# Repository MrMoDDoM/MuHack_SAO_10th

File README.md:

# MuHack_SAO_10th
Repo for the commemorative MuHack SAO fot the 10th anniversary

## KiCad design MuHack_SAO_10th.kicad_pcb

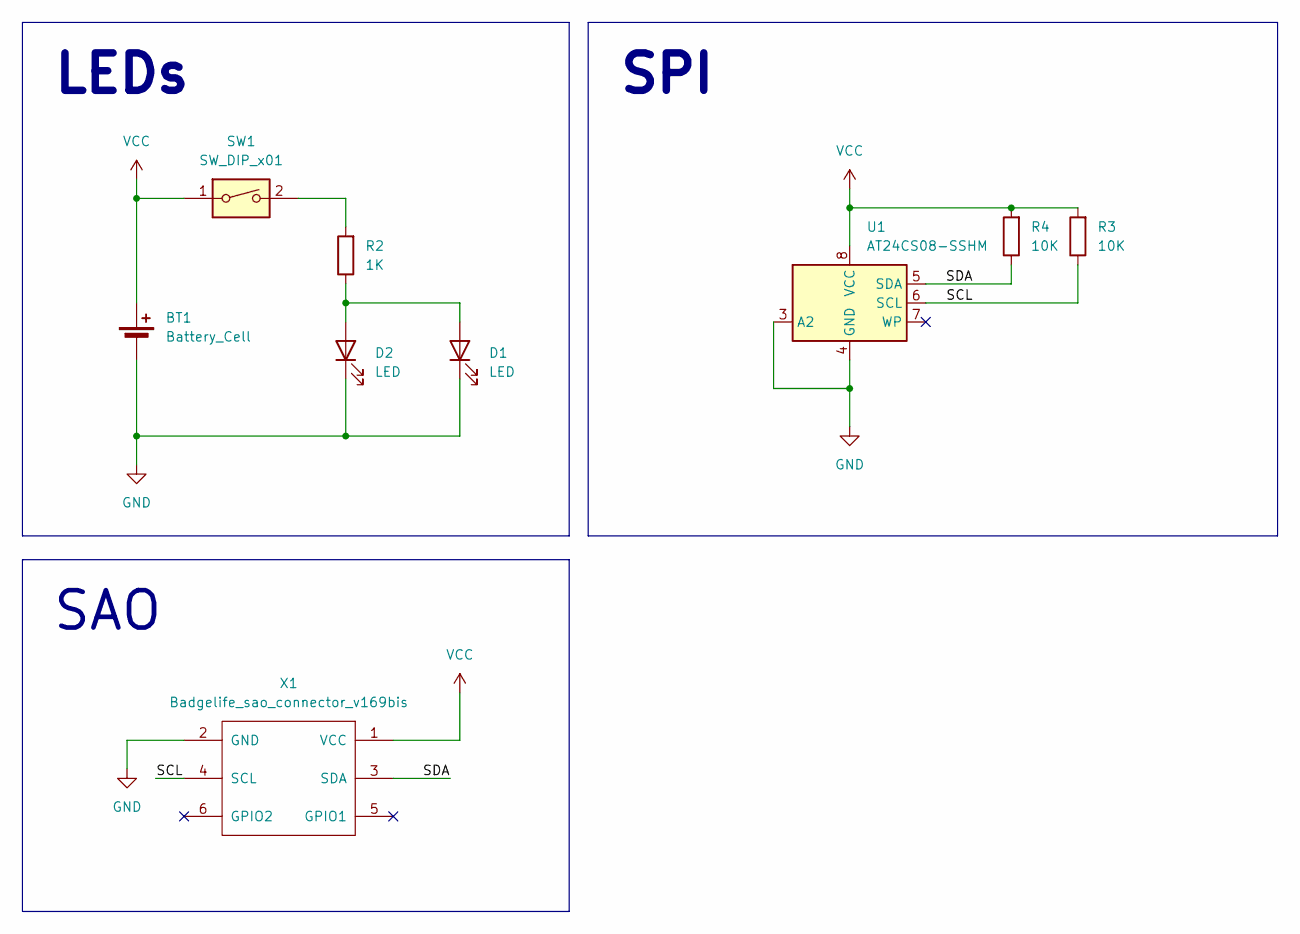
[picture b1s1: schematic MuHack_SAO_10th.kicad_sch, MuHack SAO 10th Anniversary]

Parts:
BT1: Battery_Cell; BatteryHolder_Keystone_3002_1x2032
D1, D2: LED; LED_0805_2012Metric_Pad1.15x1.40mm_HandSolder
R2: 1K; R_0805_2012Metric_Pad1.20x1.40mm_HandSolder
R3, R4: 10K; R_0805_2012Metric_Pad1.20x1.40mm_HandSolder
SW1: SW_DIP_x01; SW_SPDT_PCM12
U1: AT24CS08-SSHM; SOIC-8_3.9x4.9mm_P1.27mm
X1: Badgelife_sao_connector_v169bis; PinHeader_2x03_P2.54mm_Vertical_SMD

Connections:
/SCL: R3.1, U1.6 (SCL), X1.4 (SCL)
/SDA: R4.1, U1.5 (SDA), X1.3 (SDA)
GND: BT1.2 (-), D1.1 (K), D2.1 (K), U1.3 (A2), U1.4 (GND), X1.2 (GND)
unnamed: D1.2 (A), D2.2 (A), R2.1
unnamed: R2.2, SW1.2
VCC: BT1.1 (+), R3.2, R4.2, SW1.1, U1.8 (VCC), X1.1 (VCC)

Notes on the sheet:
LEDs
SAO
SPI

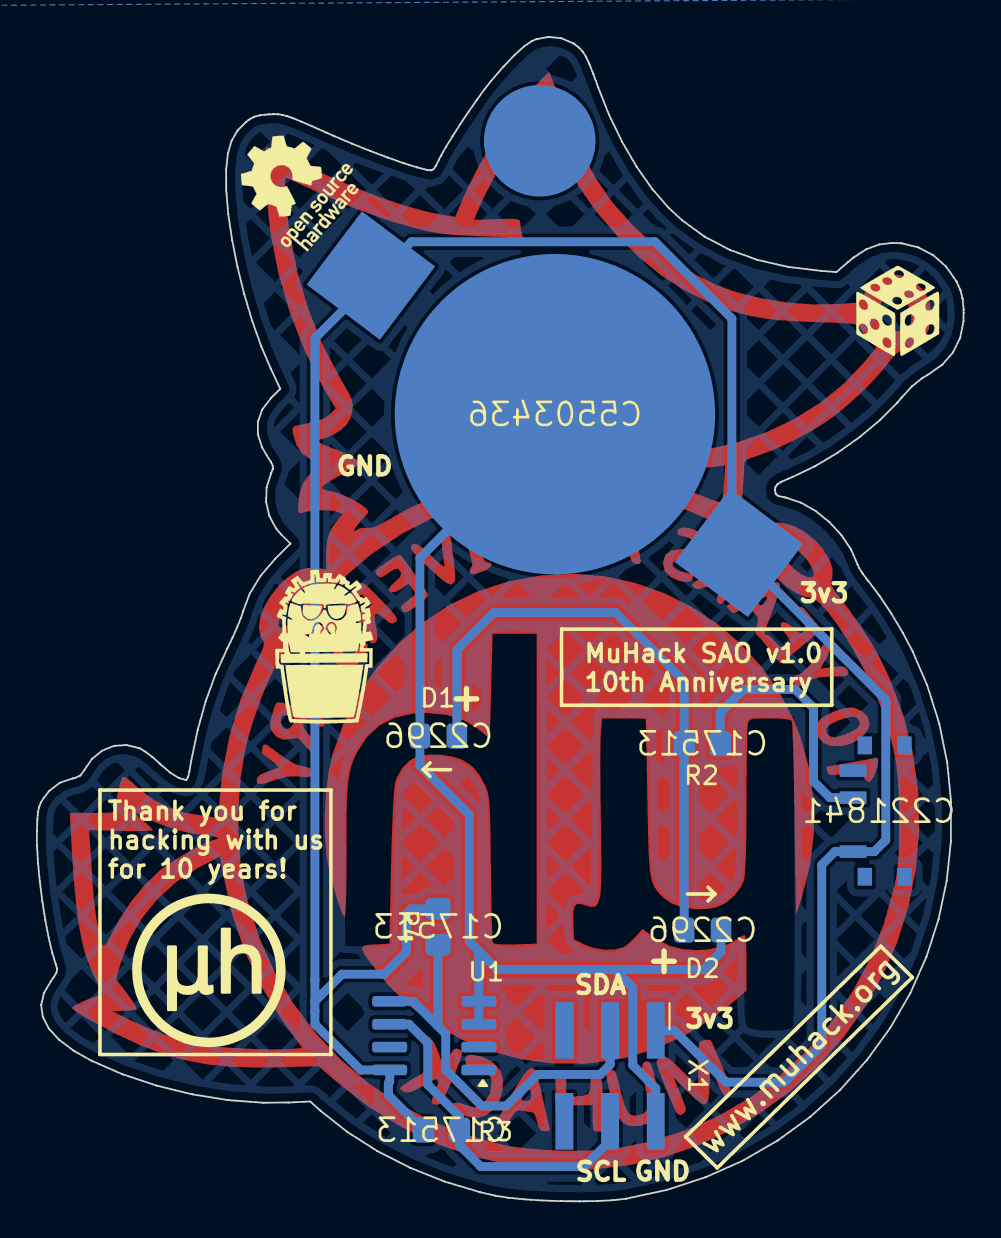
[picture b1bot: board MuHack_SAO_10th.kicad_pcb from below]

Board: 2 copper layers, 51.5 x 64.7 mm, 18 parts (11 on the bottom side), 6 nets.

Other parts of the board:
B-SolderMask_LOGO: B-SolderMask_LOGO; LOGO
BIT_LOGO: BIT_LOGO; LOGO
EdgeCut: EdgeCut; LOGO
F-Cu: F-Cu; LOGO
F-Mask: F-Mask; LOGO
KeepOut-B-SolderMask_LOGO: KeepOut-B-SolderMask_LOGO; LOGO
MUHACK_LOGO: LOGO
SilkScreen: SilkScreen; LOGO
SolderMask_LOGO: SolderMask_LOGO; LOGO

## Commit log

2024-11-23 Version v1.1
